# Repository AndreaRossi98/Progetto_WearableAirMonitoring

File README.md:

# Progetto_WearableAirMonitoring

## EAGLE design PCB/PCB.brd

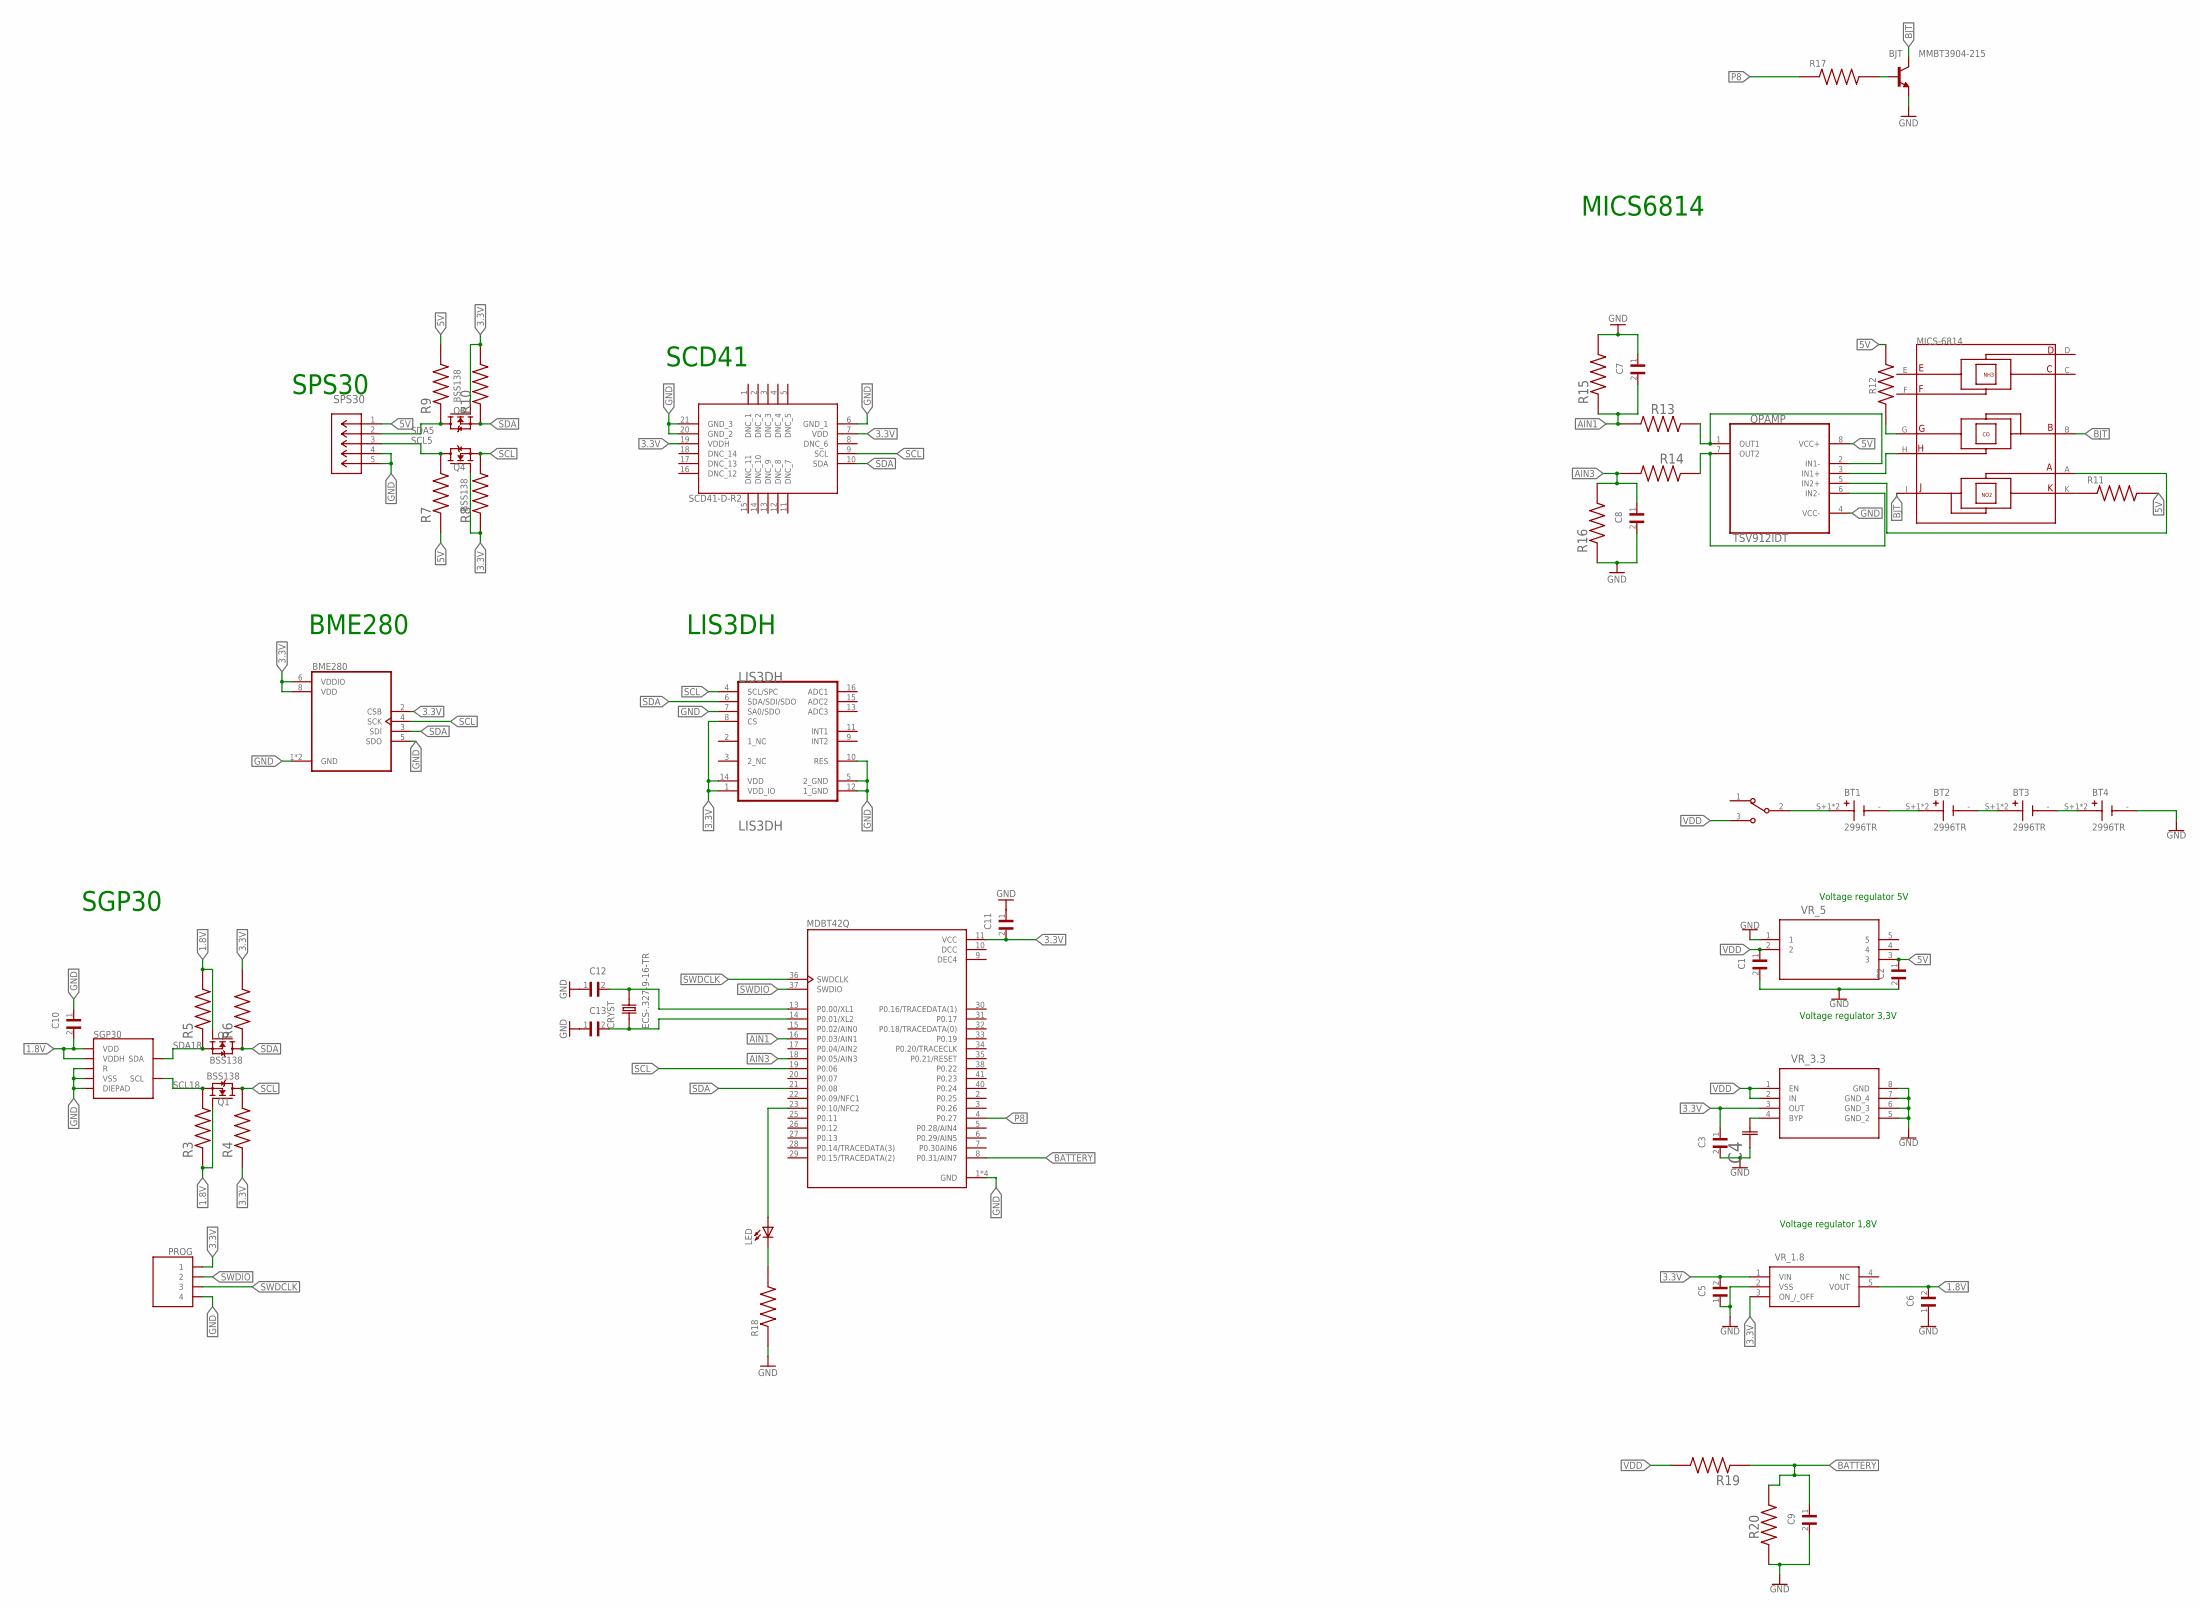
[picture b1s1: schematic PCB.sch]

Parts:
BJT: MMBT3904-215; SOT95P230X110-3N
BME280: BME280; PSON65P250X250X100-8N
BT1, BT2, BT3, BT4: 2996TR; BAT_2996TR
C1, C2, C10: C0402C104K9RACAUTO; CAPC1005X55N
C3: CL05A225MQ5NNNC; CAPC1005X55N
C4: CL05B471KB5NNNCCAP_CL05_SAM; CAP_CL05_SAM
C5, C6: JMK105BJ105KV-F; CAPC1005X55N
C7, C8, C9: CL05B103KO5NNNC; CAPC1005X55N
C11: CL05A106MP5NUNC; CAPC1005X55N
C12, C13: 04025A120FAT2A; CAPC1005X56N
CRYST: ECS-.327-9-16-TR; XTAL_ECS-.327-9-16-TR
LED: LTST-C170KRKT; DIOC200X125X110
LIS3DH: STMICROELECTRONICS_LIS3DHSTMICROELECTRONICS_LIS3D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; STMICROELECTRONICS_LIS3DH_0
MDBT42Q: 317030213; XCVR_317030213
MICS6814: MICS-6814; SENSOR_MICS-6814
OPAMP: TSV912IDT; SOIC127P600X175-8N
PROG: BG306-04-A-1-0400-X-X_REVD; GCT_BG306-04-A-1-0400-X-X_REVD
Q1, Q2, Q3, Q4: BSS138; SOT95P240X111-3N
R3, R4, R5, R6, R7, R8, R9, R10: MCS0402MC1002FE000; RESC1005X37N
R11: ERJPA2F1300X; RES_ERJPA2F1300X
R12: ERJPA2J821X; RES_ERJPA2J821X
R13, R14: ERJ-2GEJ515X; RESC1005X40N
R15, R16, R19, R20: ERJ-2GEJ106X; RESC1005X40N
R17: ERJPA2F5101X; RES_ERJPA2F5101X
R18: ERA2AEB331X; RES_ERA2AEB331X
S1: EG1213; SW_EG1213
SCD41: SCD41-D-R2; SCD41DR2
SGP30: SGP30
SPS30: S5B-ZR-SM4A-TF_(LF)_(SN)CONN_S5B-ZR-SM4A-TF_JST; CONN_S5B-ZR-SM4A-TF_JST
VR_1.8: S-1318D18-M5T1U4; SOT95P275X130-5N
VR_3.3: MIC5219-3.3YMMMSOP-8LD-PL-1_MCH; MSOP-8LD-PL-1_MCH
VR_5: MC78LC50NTRGTSOT23-5_ONS; TSOT23-5_ONS

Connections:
1.8V: C6.2, C10.2, Q1.1 (G), Q2.1 (G), R3.1, R5.2, SGP30.1 (VDD), SGP30.5 (VDDH), VR_1.8.5 (VOUT)
3.3V: BME280.2 (CSB), BME280.6 (VDDIO), BME280.8 (VDD), C3.1, C5.2, C11.2, LIS3DH.1 (VDD_IO), LIS3DH.8 (CS), LIS3DH.14 (VDD), MDBT42Q.11 (VCC), PROG.1, Q3.1 (G), Q4.1 (G), R4.1, R6.2, R8.1, R10.2, SCD41.7 (VDD), SCD41.19 (VDDH), VR_1.8.1 (VIN), VR_1.8.3 (ON_/_OFF), VR_3.3.3 (OUT)
5V: C2.1, OPAMP.8 (VCC+), R7.1, R9.2, R11.2, R12.2, SPS30.1, VR_5.3
AIN1: C7.2, MDBT42Q.16 (P0.03/AIN1), R13.1, R15.1
AIN3: C8.1, MDBT42Q.18 (P0.05/AIN3), R14.1, R16.2
BATTERY: C9.1, MDBT42Q.8 (P0.31/AIN7), R19.1, R20.1
BJT: BJT.3 (C), MICS6814.B (RH1/RS1_RED), MICS6814.J (RH1/RS1_OX)
DCC: MDBT42Q.10 (DCC)
DEC4: MDBT42Q.9 (DEC4)
GND: BJT.2 (E), BME280.1 (GND), BME280.5 (SDO), BME280.7 (GND), BT4.-, C1.2, C2.2, C3.2, C4.1, C5.1, C6.1, C7.1, C8.2, C9.2, C10.1, C11.1, C12.1, C13.1, LIS3DH.5 (2_GND), LIS3DH.7 (SA0/SDO), LIS3DH.10 (RES), LIS3DH.12 (1_GND), MDBT42Q.1 (GND), MDBT42Q.12 (GND), MDBT42Q.24 (GND), MDBT42Q.39 (GND), OPAMP.4 (VCC-), PROG.4, R15.2, R16.1, R18.1, R20.2, SCD41.6 (GND_1), SCD41.20 (GND_2), SCD41.21 (GND_3), SGP30.2 (VSS), SGP30.4 (R), SGP30.DIEPAD, SPS30.4, SPS30.5, VR_1.8.2 (VSS), VR_3.3.5 (GND_2), VR_3.3.6 (GND_3), VR_3.3.7 (GND_4), VR_3.3.8 (GND), VR_5.1
LED: LED.+, MDBT42Q.23 (P0.10/NFC2)
unnamed: BT1.-, BT2.S+1 (+), BT2.S+2 (+)
unnamed: MICS6814.A (RS2), OPAMP.5 (IN2+)
unnamed: BT2.-, BT3.S+1 (+), BT3.S+2 (+)
unnamed: OPAMP.6 (IN2-), OPAMP.7 (OUT2), R14.2
unnamed: OPAMP.1 (OUT1), OPAMP.2 (IN1-), R13.2
unnamed: LED.-, R18.2
unnamed: MICS6814.H (RS2_RED), OPAMP.3 (IN1+)
unnamed: MICS6814.G (RH2_RED), R12.1
unnamed: MICS6814.K (RH2_OX), R11.1
unnamed: C4.2, VR_3.3.4 (BYP)
unnamed: BJT.1 (B), R17.2
unnamed: C12.2, CRYST.2, MDBT42Q.13 (P0.00/XL1)
unnamed: C13.2, CRYST.1, MDBT42Q.14 (P0.01/XL2)
unnamed: BT3.-, BT4.S+1 (+), BT4.S+2 (+)
unnamed: BT1.S+1 (+), BT1.S+2 (+), S1.2
P8: MDBT42Q.4 (P0.27), R17.1
SCL: BME280.4 (SCK), LIS3DH.4 (SCL/SPC), MDBT42Q.19 (P0.06), Q1.3 (D), Q4.2 (S), R4.2, R8.2, SCD41.9 (SCL)
SCL5: Q4.3 (D), R7.2, SPS30.3
SCL18: Q1.2 (S), R3.2, SGP30.6 (SCL)
SDA: BME280.3 (SDI), LIS3DH.6 (SDA/SDI/SDO), MDBT42Q.21 (P0.08), Q2.3 (D), Q3.2 (S), R6.1, R10.1, SCD41.10 (SDA)
SDA5: Q3.3 (D), R9.1, SPS30.2
SDA18: Q2.2 (S), R5.1, SGP30.3 (SDA)
SWDCLK: MDBT42Q.36 (SWDCLK), PROG.3
SWDIO: MDBT42Q.37 (SWDIO), PROG.2
VDD: C1.1, R19.2, S1.3, VR_3.3.1 (EN), VR_3.3.2 (IN), VR_5.2

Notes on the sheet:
SCD41
SPS30
BME280
SGP30
LIS3DH
Voltage regulator 5V
Voltage regulator 3,3V
Voltage regulator 1,8V
MICS6814

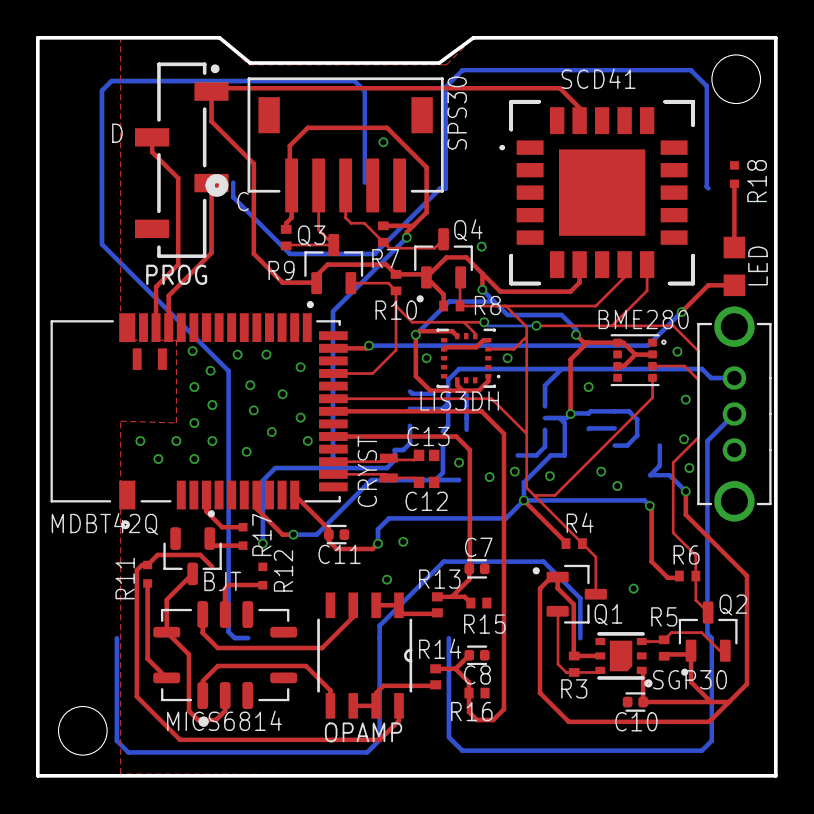
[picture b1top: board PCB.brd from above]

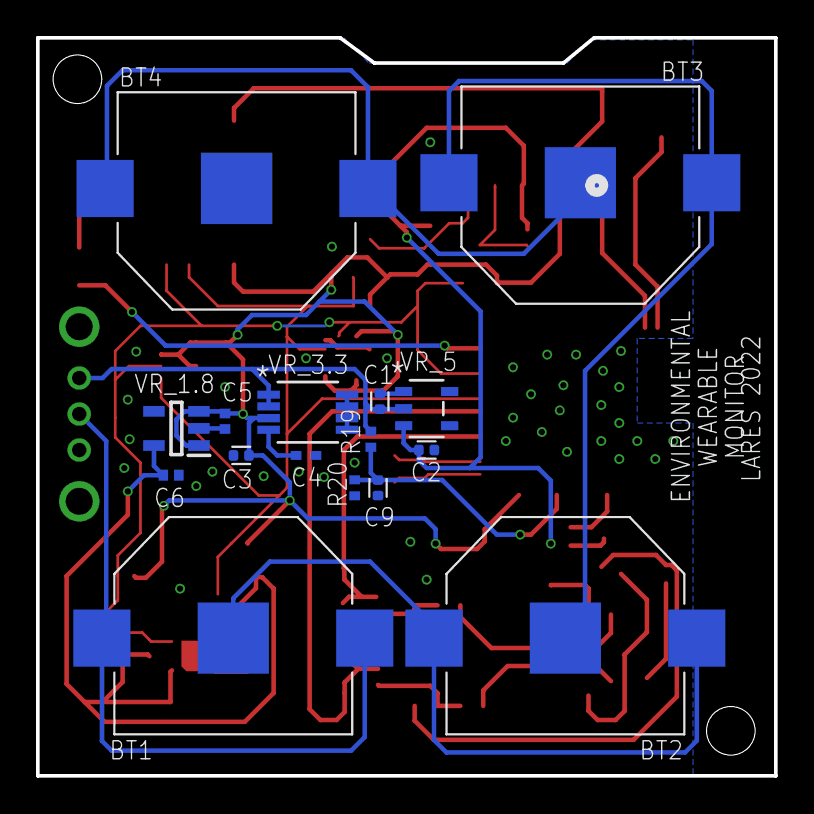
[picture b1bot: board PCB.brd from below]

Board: 4 copper layers, 41.0 x 41.0 mm, 55 parts (16 on the bottom side), 34 nets.

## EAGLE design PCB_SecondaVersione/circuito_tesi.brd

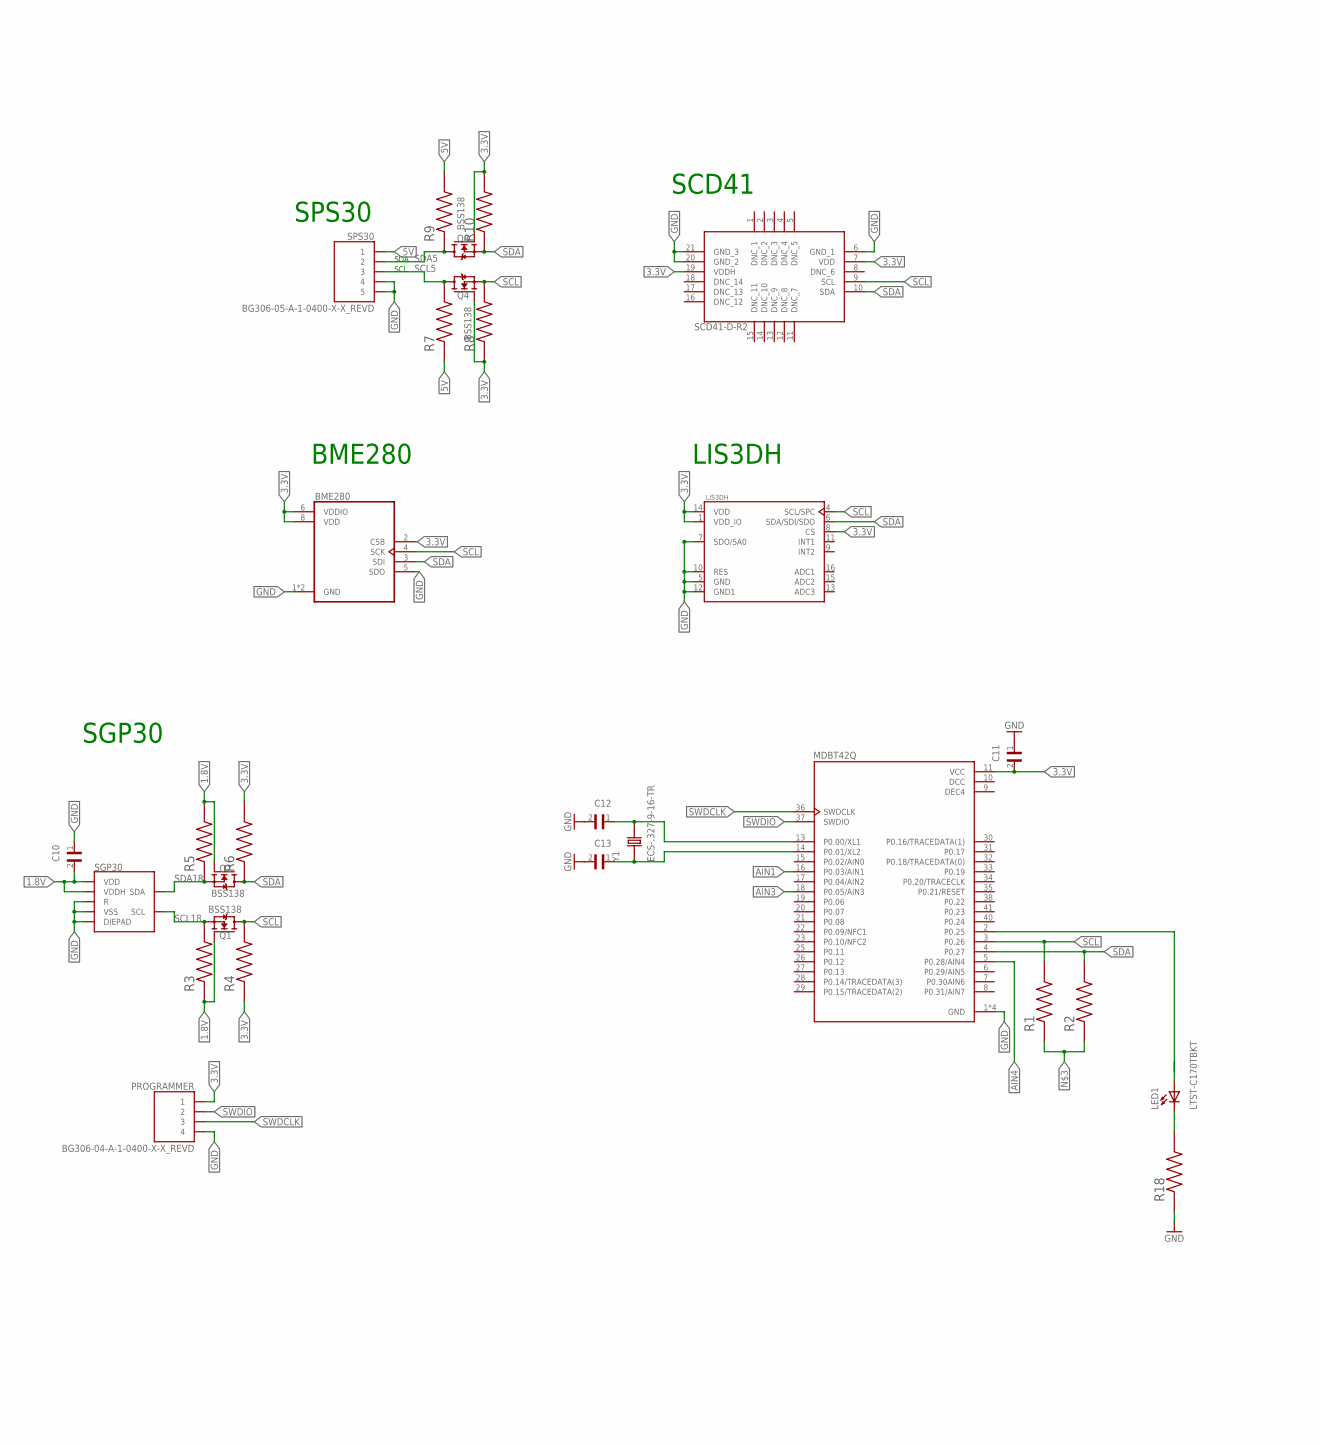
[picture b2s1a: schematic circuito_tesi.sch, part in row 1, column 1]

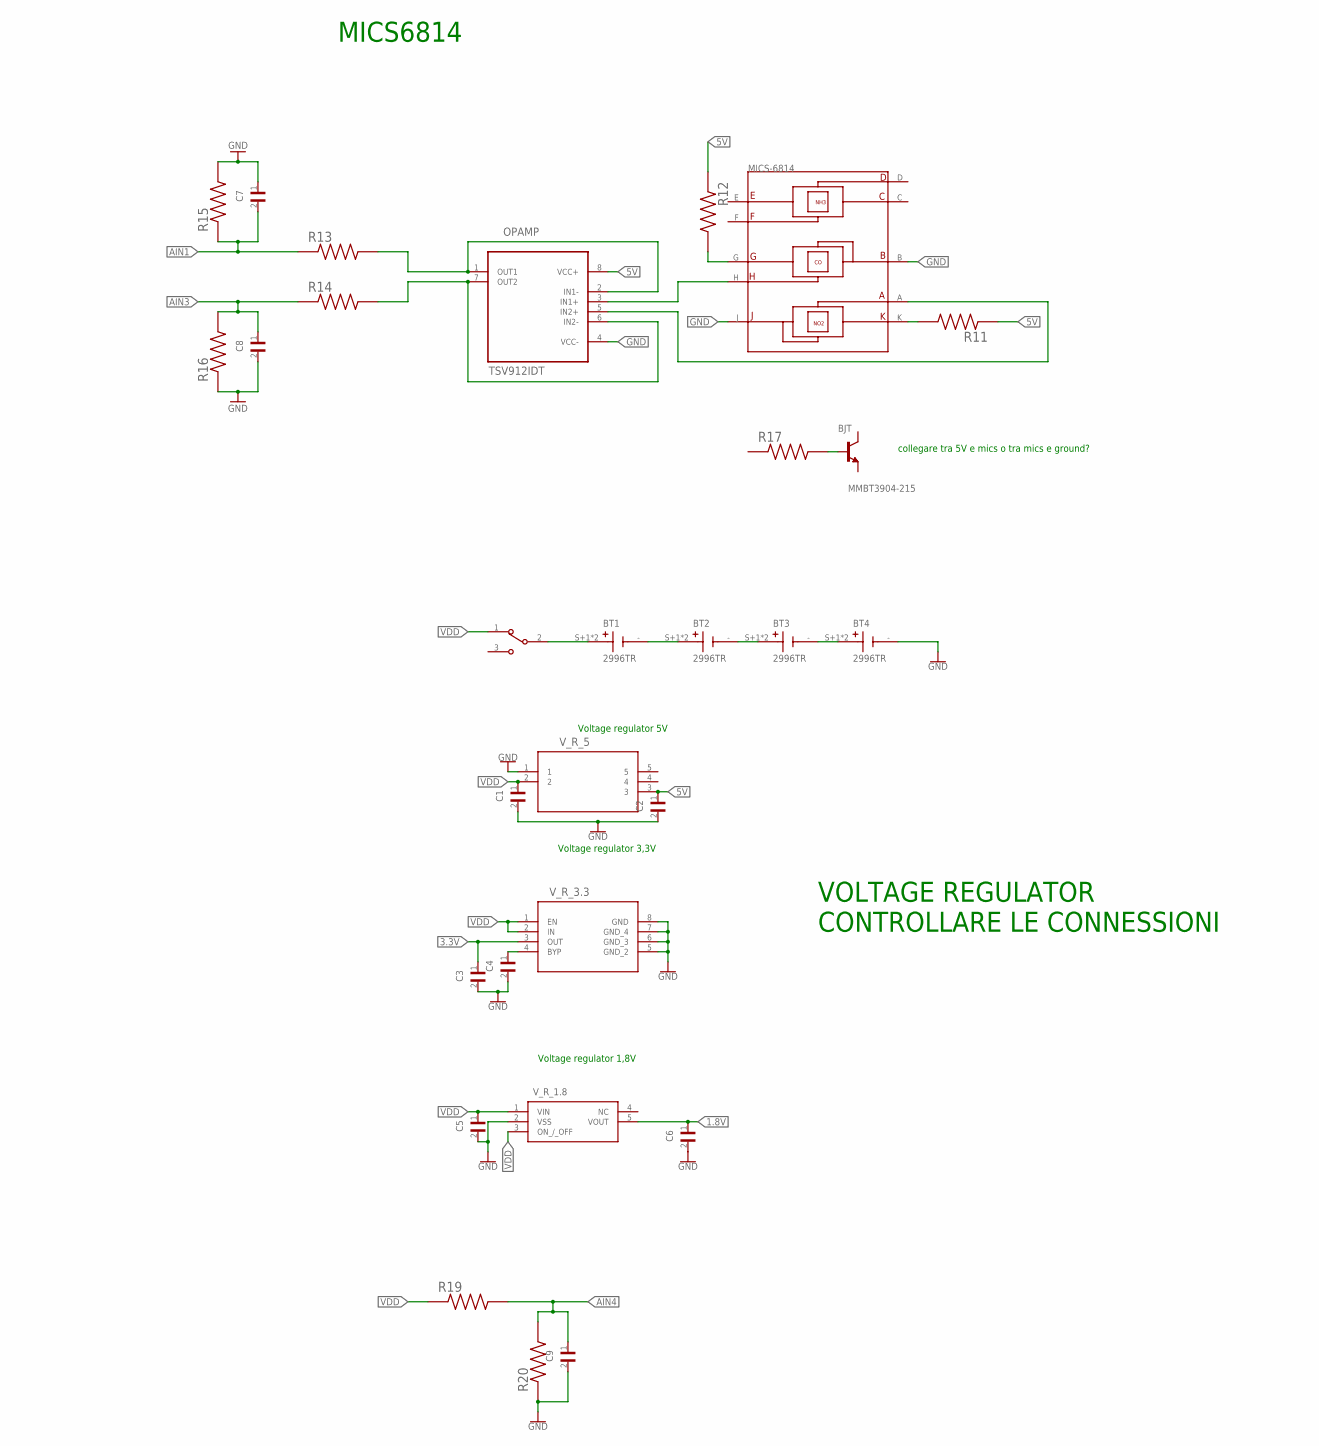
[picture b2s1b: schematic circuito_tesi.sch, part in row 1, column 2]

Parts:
BJT: MMBT3904-215; SOT95P230X110-3N
BT1, BT2, BT3, BT4: 2996TR; BAT_2996TR
C1, C2, C3, C4, C5, C6, C7, C8, C9, C10, C11, C12, C13: C0402H102J5GACTU; CAPC1005X55N
IC1: SCD41-D-R2; SCD41DR2
LED1: LTST-C170TBKT; DIOC200X125X110
MDBT42Q: 317030213; XCVR_317030213
OPAMP: TSV912IDT; SOIC127P600X175-8N
PROGRAMMER: BG306-04-A-1-0400-X-X_REVD; GCT_BG306-04-A-1-0400-X-X_REVD
Q1, Q2, Q3, Q4: BSS138; SOT95P240X111-3N
R1, R2, R3, R4, R5, R6, R7, R8, R9, R10, R11, R12, R13, R14, R15, R16, R17, R18, R19, R20: 8-1879333-9; RESC1005X35N
S1: EG1213; SW_EG1213
SGP30: SGP30
SPS30: BG306-05-A-1-0400-X-X_REVD; GCT_BG306-05-A-1-0400-X-X_REVD
U3: MICS-6814; SENSOR_MICS-6814
U6: BME280; PSON65P250X250X100-8N
U7: LIS3DH; PQFN50P300X300X100-16N
V_R_1.8: S-1318D18-M5T1U4; SOT95P275X130-5N
V_R_3.3: MIC5219-3.3YMMMSOP-8LD-PL-1_MCH; MSOP-8LD-PL-1_MCH
V_R_5: MC78LC50NTRGTSOT23-5_ONS; TSOT23-5_ONS
Y1: ECS-.327-9-16-TR; XTAL_ECS-.327-9-16-TR

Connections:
1.8V: C6.1, C10.2, Q1.1 (G), Q2.1 (G), R3.1, R5.2, SGP30.1 (VDD), SGP30.5 (VDDH), V_R_1.8.5 (VOUT)
3.3V: C3.1, C11.2, IC1.7 (VDD), IC1.19 (VDDH), MDBT42Q.11 (VCC), PROGRAMMER.1, Q3.1 (G), Q4.1 (G), R4.1, R6.2, R8.1, R10.2, U6.2 (CSB), U6.6 (VDDIO), U6.8 (VDD), U7.1 (VDD_IO), U7.8 (CS), U7.14 (VDD), V_R_3.3.3 (OUT)
5V: C2.1, OPAMP.8 (VCC+), R7.1, R9.2, R11.1, R12.1, SPS30.1, V_R_5.3
AIN1: C7.2, MDBT42Q.16 (P0.03/AIN1), R13.1, R15.1
AIN3: C8.1, MDBT42Q.18 (P0.05/AIN3), R14.1, R16.2
AIN4: C9.1, MDBT42Q.5 (P0.28/AIN4), R19.2, R20.2
DCC: MDBT42Q.10 (DCC)
DEC4: MDBT42Q.9 (DEC4)
GND: BT4.-, C1.2, C2.2, C3.2, C4.2, C5.2, C6.2, C7.1, C8.2, C9.2, C10.1, C11.1, C12.2, C13.2, IC1.6 (GND_1), IC1.20 (GND_2), IC1.21 (GND_3), MDBT42Q.1 (GND), MDBT42Q.12 (GND), MDBT42Q.24 (GND), MDBT42Q.39 (GND), OPAMP.4 (VCC-), PROGRAMMER.4, R15.2, R16.1, R18.1, R20.1, SGP30.2 (VSS), SGP30.4 (R), SGP30.DIEPAD, SPS30.4, SPS30.5, U3.B (RH1/RS1_RED), U3.J (RH1/RS1_OX), U6.1 (GND), U6.5 (SDO), U6.7 (GND), U7.5 (GND), U7.7 (SDO/SA0), U7.10 (RES), U7.12 (GND1), V_R_1.8.2 (VSS), V_R_3.3.5 (GND_2), V_R_3.3.6 (GND_3), V_R_3.3.7 (GND_4), V_R_3.3.8 (GND), V_R_5.1
unnamed: BT1.-, BT2.S+1 (+), BT2.S+2 (+)
unnamed: R1.1, R2.1
unnamed: BT2.-, BT3.S+1 (+), BT3.S+2 (+)
unnamed: OPAMP.5 (IN2+), U3.A (RS2)
unnamed: OPAMP.6 (IN2-), OPAMP.7 (OUT2), R14.2
unnamed: OPAMP.1 (OUT1), OPAMP.2 (IN1-), R13.2
unnamed: LED1.-, R18.2
unnamed: OPAMP.3 (IN1+), U3.H (RS2_RED)
unnamed: R12.2, U3.G (RH2_RED)
unnamed: R11.2, U3.K (RH2_OX)
unnamed: C4.1, V_R_3.3.4 (BYP)
unnamed: BJT.1 (B), R17.2
unnamed: C12.1, MDBT42Q.13 (P0.00/XL1), Y1.2
unnamed: C13.1, MDBT42Q.14 (P0.01/XL2), Y1.1
unnamed: LED1.+, MDBT42Q.2 (P0.25)
unnamed: BT3.-, BT4.S+1 (+), BT4.S+2 (+)
unnamed: BT1.S+1 (+), BT1.S+2 (+), S1.2
SCL: IC1.9 (SCL), MDBT42Q.3 (P0.26), Q1.3 (D), Q4.2 (S), R1.2, R4.2, R8.2, U6.4 (SCK), U7.4 (SCL/SPC)
SCL5: Q4.3 (D), R7.2, SPS30.3
SCL18: Q1.2 (S), R3.2, SGP30.6 (SCL)
SDA: IC1.10 (SDA), MDBT42Q.4 (P0.27), Q2.3 (D), Q3.2 (S), R2.2, R6.1, R10.1, U6.3 (SDI), U7.6 (SDA/SDI/SDO)
SDA5: Q3.3 (D), R9.1, SPS30.2
SDA18: Q2.2 (S), R5.1, SGP30.3 (SDA)
SWDCLK: MDBT42Q.36 (SWDCLK), PROGRAMMER.3
SWDIO: MDBT42Q.37 (SWDIO), PROGRAMMER.2
VDD: C1.1, C5.1, R19.1, S1.1, V_R_1.8.1 (VIN), V_R_1.8.3 (ON_/_OFF), V_R_3.3.1 (EN), V_R_3.3.2 (IN), V_R_5.2

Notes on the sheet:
SCL
SDA
SCD41
SPS30
BME280
SGP30
LIS3DH
Voltage regulator 5V
Voltage regulator 3,3V
Voltage regulator 1,8V
VOLTAGE REGULATOR CONTROLLARE LE CONNESSIONI
MICS6814
collegare tra 5V e mics o tra mics e ground?

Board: 2 copper layers, 57 parts (8 on the bottom side), 33 nets, no tracks yet.

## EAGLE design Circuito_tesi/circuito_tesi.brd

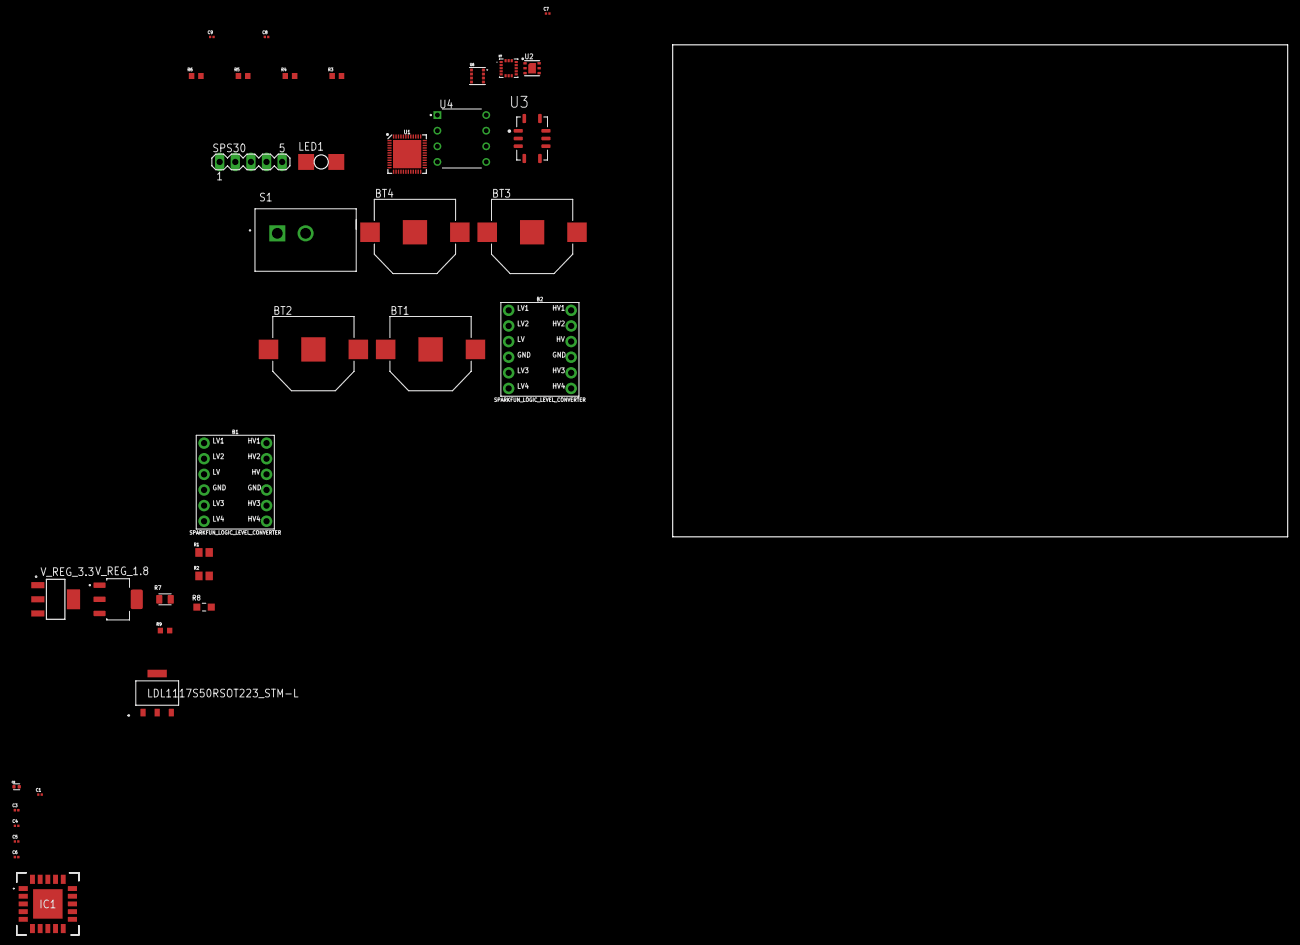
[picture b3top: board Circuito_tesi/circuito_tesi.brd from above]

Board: 2 copper layers, 100.0 x 80.0 mm, 37 parts (0 on the bottom side), 25 nets, no tracks yet.

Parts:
B1, B2: SPARKFUN_LOGIC_LEVEL_CONVERTER
BT1, BT2, BT3, BT4: 2996TR; BAT_2996TR
C1, C7: GRM033C80J104KE15D; CAPC0603X33N
C2: CL05A106MP5NUNC; CAPC1005X55N
C3, C6: GRM035R60G475ME15D; CAPC0603X55N
C4, C5: GRM033R60J105MEA2D; CAPC0603X35N
C8, C9: GRM033R60J103KA01D; CAPC0603X33N
IC1: SCD41-D-R2; SCD41DR2
LED1: LAP4-BOTTOM; P47F-BOTTOM
R1, R2: RNCP0805FTD10K0; RESC2012X60N
R3, R4: RMCF0603FT10M0; RESC1508X55N
R5, R6: RMCF0603FT5M10; RESC1508X55N
R7: RP73PF2A130RBTDF; RESC2012X65N
R8: ERA6VEB8200V; RES_ERA6VEB8200V
R9: RNCF0603DTE820R; RESC1508X55N
S1: GF-123-0054; SW_GF-123-0054
SPS30: MA05-1
U1: NRF52832; QFN48-6X6MM
U2: SGP30
U3: MICS-6814; SENSOR_MICS-6814
U4: OPA2277PA; DIP794W45P254L959H508Q8
U6: BME280; PSON65P250X250X100-8N
U7: LIS3DH; PQFN50P300X300X100-16N
V_REG_1.8: MCP1825S-1802E/DB; SOT230P700X180-4N
V_REG_3.3: LD1117S33TR; SOT230P700X180-4N
V_REG_5: LDL1117S50RSOT223_STM-L; SOT223_STM-L

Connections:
1.8V: B2.LV, C5.2, C7.1, U2.1, U2.5, U7.1, U7.8, U7.14, V_REG_1.8.3
3.3: B1.LV, B2.HV, C2.1, IC1.7, IC1.19, R1.2, R2.2, U1.13, U1.36, U1.48, U6.2, U6.6, U6.8, V_REG_3.3.2, V_REG_3.3.4
5V: B1.HV, C3.2, C6.2, R7.2, R8.2, SPS30.1, U4.8, V_REG_1.8.1, V_REG_5.4
GND: B1.GND1, B1.GND2, B2.GND1, B2.GND2, BT4.-, C1.1, C2.2, C3.1, C4.1, C5.1, C6.1, C7.2, C8.1, C9.1, IC1.6, IC1.20, IC1.21, R3.1, R4.1, R9.1, SPS30.4, SPS30.5, U2.2, U2.4, U2.DIEPAD, U3.B, U3.J, U4.4, U6.1, U6.5, U6.7, U7.5, U7.7, U7.10, U7.12, V_REG_1.8.2, V_REG_1.8.4, V_REG_3.3.1, V_REG_5.1
unnamed: B1.HV3, SPS30.2
unnamed: BT1.-, BT2.S+1, BT2.S+2
unnamed: B1.HV4, SPS30.3
unnamed: BT2.-, BT3.S+1, BT3.S+2
unnamed: BT3.-, BT4.S+1, BT4.S+2
unnamed: U3.A, U4.5
unnamed: R6.2, U4.6, U4.7
unnamed: LED1.C, R9.2
unnamed: U3.H, U4.3
unnamed: R8.1, U3.G
unnamed: R7.1, U3.K
unnamed: C9.2, R4.2, R6.1, U1.5
unnamed: C8.2, R3.2, R5.2, U1.7
unnamed: BT1.S+1, BT1.S+2, S1.1
unnamed: B2.LV3, U2.3, U7.6
unnamed: LED1.A, U1.28
unnamed: R5.1, U4.1, U4.2
unnamed: B2.LV4, U2.6, U7.4
SCL: B1.LV4, B2.HV4, IC1.9, R2.1, U1.22, U6.4
SDA: B1.LV3, B2.HV3, IC1.10, R1.1, U1.21, U6.3
VDD: C1.2, C4.2, S1.2, V_REG_3.3.3, V_REG_5.3

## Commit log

2022-04-12 Aggiunti tutti i file
2022-04-13 Sistemata lettura ogni interrupt
2022-04-13 Attivato saadc
2022-04-20 Aggiunta lettura MICS6814
2022-04-21 Aggiunta conversione valori mics
2022-04-22 Completato schematico (resistenze non corrette)
2022-04-27 modifica board
2022-04-28 Aggiunti circuiti su board
2022-04-28 Aggiunte resistenze e condensatori smd
2022-05-03 Aggiunto BME280
2022-05-04 Sistemato file bme280
2022-05-05 Aggiunto BME280 e SGP30
2022-05-09 Aggiunto ACCELEROMETRO
2022-05-10 Accelerometro funzionante
2022-05-11 Aggiunte funzioni di inizializzazione e settaggio sensori
2022-05-11 Cambiate resistenze a 1/4 W max
2022-05-13 Aggiunte nuovi condensatori e voltage regulator
2022-05-18 Impostato schema generale
2022-05-18 Aggiunta stampa valolri
2022-05-18 Aggiunto SCD4x al circuito
2022-05-19 Aggiunto WFI
2022-05-21 Aggiunta PCB 4.1x4.1
2022-05-22 PCB prima prova
2022-05-26 Corretta formula concentrazione CO
2022-05-29 Seconda versione PCB
2022-05-29 Sistemato circuito
2022-05-29 Inizio PCB
2022-05-29 Aggiunto SGP30
2022-05-30 Aggiunto Voltage Regulators
2022-05-31 Aggiunte capacità 0805
2022-05-31 Sistemati nomi su Eagle
2022-06-01 Aggiunti case 0402
2022-06-01 Posizionamento su PCB
2022-06-02 Inizio board
2022-06-03 Impostato posizione generale
2022-06-04 PCB finita seconda versione
2022-06-04 Nuova versione PCB
2022-06-05 aggiunte piste
2022-06-06 Colleganenti PCB fatti
2022-06-06 Connessioni OK
2022-06-06 Cambiato piedino SPS30
2022-06-06 Sistemate alcune piste
2022-06-07 Sistemate piste PCB
2022-06-07 Aggiunti piani di Ground
2022-06-07 Prototipo finale
2022-06-07 Cambiato collegamento BJT
2022-06-08 Resistenze con valore esatto
2022-06-08 Messi condensatori corretti
2022-06-08 Sistemati dei dettagli
2022-06-08 Tolto resistenze pull up I2C
2022-06-09 Aggiunto DRC
2022-06-09 Sistemata posizione componenti
2022-06-09 Aggiunti nomi
2022-06-09 Controllo DRC
2022-06-10 Sistemati dettagli
2022-06-13 Prove di thermal vias
2022-06-13 Cambiato layer alle scritte
2022-06-13 Aggiunti thermal vias
2022-06-13 Foro da 2.7
2022-06-13 Modifiche per DRC
2022-06-28 Aggiunta nuova versione PCB
2022-06-28 Modifiche
2022-06-28 Sistemate alcune linee
2022-06-28 Sistemato spessore connessioni
2022-06-29 Aggiunta APP e collegata a Firebase
2022-06-29 Introdotto scelta Environmental Monitor
2022-06-29 Piccole modifiche grafiche
2022-06-30 Prima prova selezione opzione
2022-07-01 Sistemato scelta sensori
2022-07-01 Pulito il codice
2022-07-01 Inizio parte environmental monitor
2022-07-04 Continuo parte environmental
2022-07-05 Modifiche Environmental
2022-07-05 Schermata Environmental Monitor funzionante
2022-07-06 Cambiato nome a variabile
2022-07-07 Aggiunto file per vedere valori
2022-07-10 Sistemato visione dati
2022-07-20 modifiche per vedere connessione
2022-07-20 Parte iniziale case con SPS30
2022-07-20 Sistemato dispaly per cellulare Eli
2022-07-21 Aggiunta schermate recording
2022-07-21 Schermata
2022-07-21 Aggiunta visione dei valori
2022-07-21 Sistemato visualizzazione dati
2022-07-21 Comunicazione tra i due ok
2022-07-22 Invio doppio pacchetto
2022-07-22 Salvataggio dati su file ok
2022-07-26 Aggiunta geolocalizzazione e salvata su file
2022-07-26 Corretto scrittura su Firebase
2022-07-26 Eliminate vecchie versioni PCB
2022-07-26 cambiato device type
2022-07-27 Funziona geo
2022-07-27 Aggiunta pressione a schermo
2022-07-27 migliorato gestione doppio pacchetto
2022-07-27 Ottimizzato doppio pacchetto
2022-07-27 aggiustato visione dati a schermo
2022-07-27 Sistemato github
2022-07-28 sistemata visione
2022-07-28 Firebase sembra funzionare
2022-07-30 Firebase funziona
2022-07-30 Aggiunta schermata Maps
2022-07-30 Visione di un punto su Maps
2022-07-30 Problema di visione dati su Maps
2022-07-31 Corretta visione file per Maps
2022-07-31 Marker su Maps funzionante
2022-07-31 Problemi tasto chiusura Maps
2022-08-01 Sistemata uscita da Maps
2022-08-01 Qua funziona
2022-08-02 Aggiunta PCB 3D
2022-08-02 Aggiunta PCB a case
2022-08-03 PCB 3D
2022-08-14 Parte sopra case
2022-08-14 Sistemate dimensioni
2022-08-15 Inizio gestione triplice pacchetto
2022-08-16 Corretta gestione tre pacchetti da micro_con_ANT
2022-08-16 piccole modifiche
2022-08-16 Aggiunta parte mediana case
2022-08-31 Gestione 3 pacchetti ok
2022-08-31 Spezzamento valori per invio
2022-09-01 Aggiunta opzione mappa su modalità timer
2022-09-03 Chiusura case
2022-09-03 Idea braccetti laterali
2022-09-04 Aggiunte alette
2022-09-04 Aggiunte idee per fori
2022-09-05 Aggiunte chiusure laterali
2022-09-05 Idee dei buchi
2022-09-05 Aggiunti fori
2022-09-05 Buchi su tutti i lati
2022-09-05 Aggiunte I/O
2022-09-05 Stampa case
2022-09-06 Gestione treiplice pacchetto e salvataggio su file fatto
2022-09-07 Aggiunta salvataggio pacchetti parzialmente arrivati
2022-09-07 Attivati sensori
2022-09-09 Adattato codice a PCB
2022-09-09 Aggiunta saturation + environmental
2022-09-09 Inizio Saturimetro + Environmental
2022-09-10 Saturation + Environmental
2022-09-10 Problemi con Maps
2022-09-11 gestione ANT doppio canale
2022-09-11 Problemi nel doppio canale ant
2022-09-12 Correzioni App Environmental
2022-09-12 Corretta gestione scrittura su file
2022-09-13 Inizio IMUs + Environmental
2022-09-13 Layout IMUs + Environmental
2022-09-13 Layout environmental + IMUs
2022-09-13 Layout IMUs Saturation Environmental
2022-09-13 Separata gestione salvataggio
2022-09-14 Attenzione pacchetti in hex
2022-09-14 Corretta gestione triplice pacchetto
2022-09-14 Gestione doppio canale
2022-09-14 modifichine
2022-09-17 Gestion doppio canale Pulse Ox + Environmental
2022-09-17 Gestione pacchetto arrivato
2022-09-18 Nuovo case
2022-09-18 modifiche case
2022-09-18 case
2022-09-19 cambiato periodo ant
2022-09-20 parte sotto
2022-09-20 braccetti
2022-09-20 fissaggio PCB
2022-09-20 buchi
2022-09-20 Gestione doppio canale OK
2022-09-20 gestione dato PM decimale intero
2022-09-20 Saturation + Environmental OK
2022-09-21 IMUs + Environmental
2022-09-21 canale doppio IMUs + Environmental
2022-09-21 Gestione doppio canale IMU+Saturation+Environmental
2022-09-21 Maps
2022-09-21 salvataggio dati saturation + envionmental
2022-09-22 Sistemato case
2022-09-22 Maps funziona
2022-09-23 ok triplice pacchetto
2022-09-23 IMUs + saturimetro + environmental doppio canale
2022-09-23 Umidità assoluta
2022-09-26 Maps timer
2022-09-27 azzerata visione dati precedenti
2022-09-27 sistemato problema IMUs
2022-09-27 visione due decimali NO2 e CO
2022-09-28 colore scritte
2022-09-28 gestione LED
2022-09-28 IMUs + Environmental ok
2022-09-28 imu + saturation + environmental
2022-09-29 connessione a tutti i dispositivi ok
2022-09-29 Sistemata scritta grafica
2022-09-30 SPS30 funzionamento
2022-10-01 localizzazione permesso
2022-10-02 ok geolocalizzazione
2022-10-02 geolocalizzazione in tutti
2022-10-02 sistemato geolocalizzazione
2022-10-04 sistemata data e ora
2022-10-05 ok gestione LED
2022-10-05 ANT a 2 sec
2022-10-11 modifiche secondarie App
2022-10-22 codici elaborazione
2022-10-23 codice dati
2022-10-29 file
2022-11-21 Modifiche codice analisi
2022-12-07 Cambiato account Firebase associato

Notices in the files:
parts and their libraries:
SparkFun-Boards: Licensing: Creative Commons ShareAlike 4.0 International - https://creativecommons.org/licenses/by-sa/4.0
COPYRIGHT: Copyright (C) 2022 Ultra Librarian. All rights reserved.
